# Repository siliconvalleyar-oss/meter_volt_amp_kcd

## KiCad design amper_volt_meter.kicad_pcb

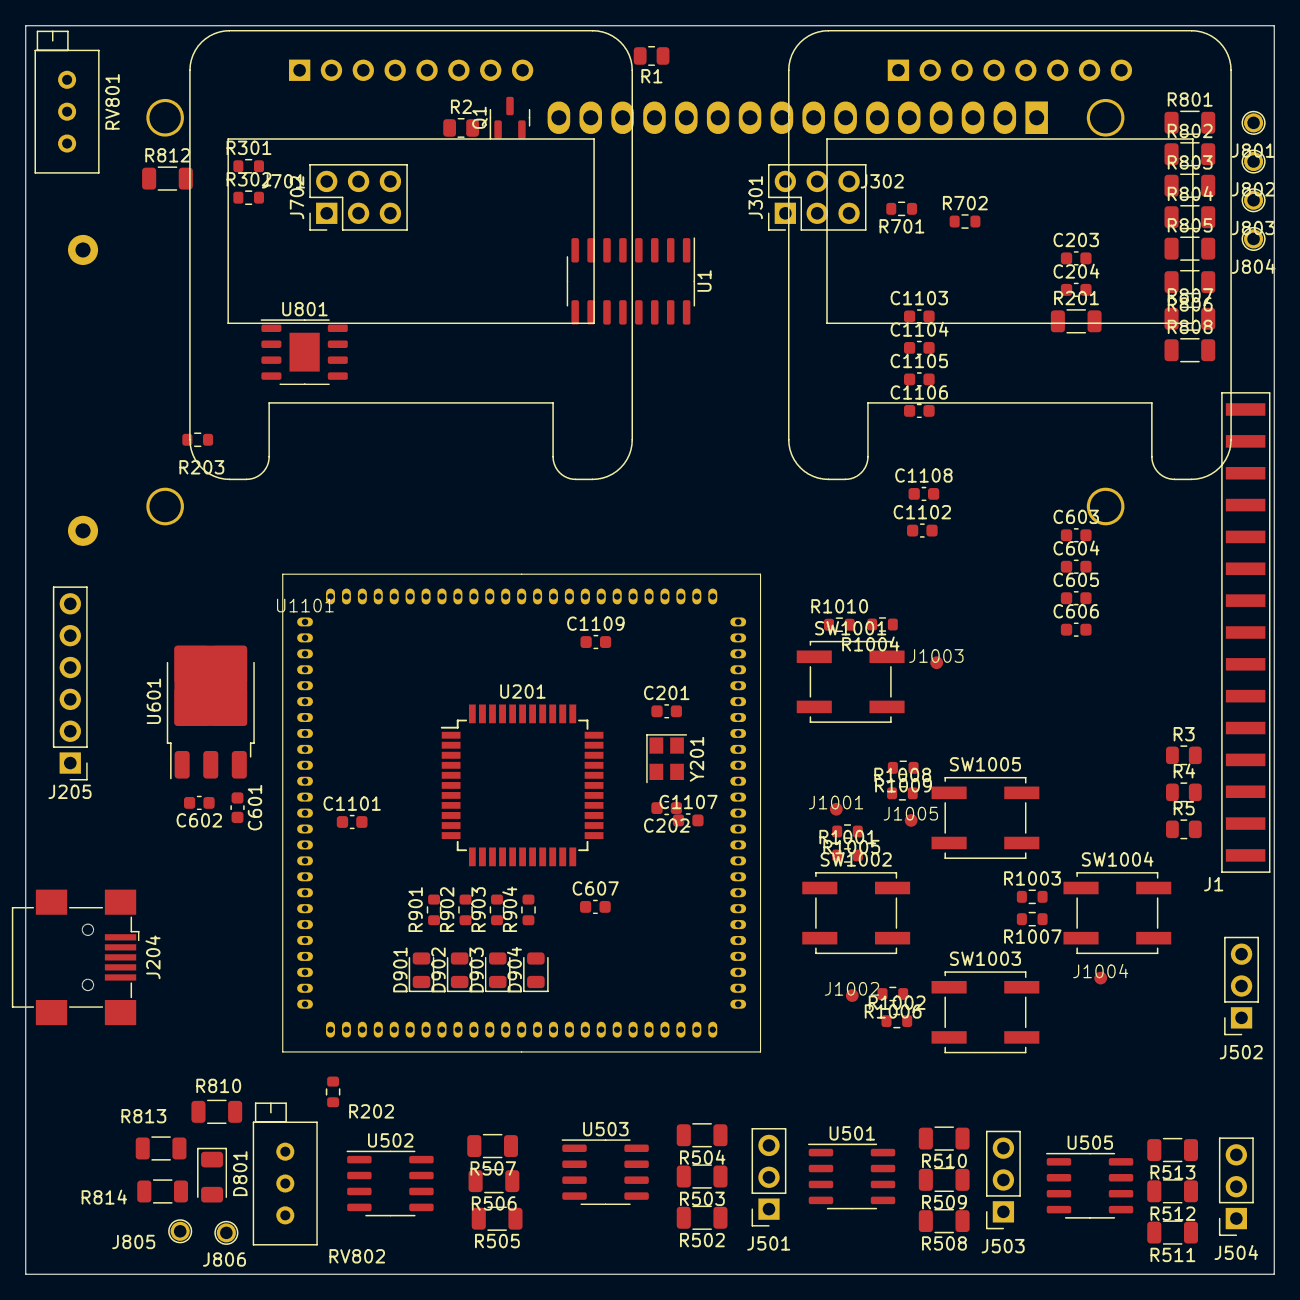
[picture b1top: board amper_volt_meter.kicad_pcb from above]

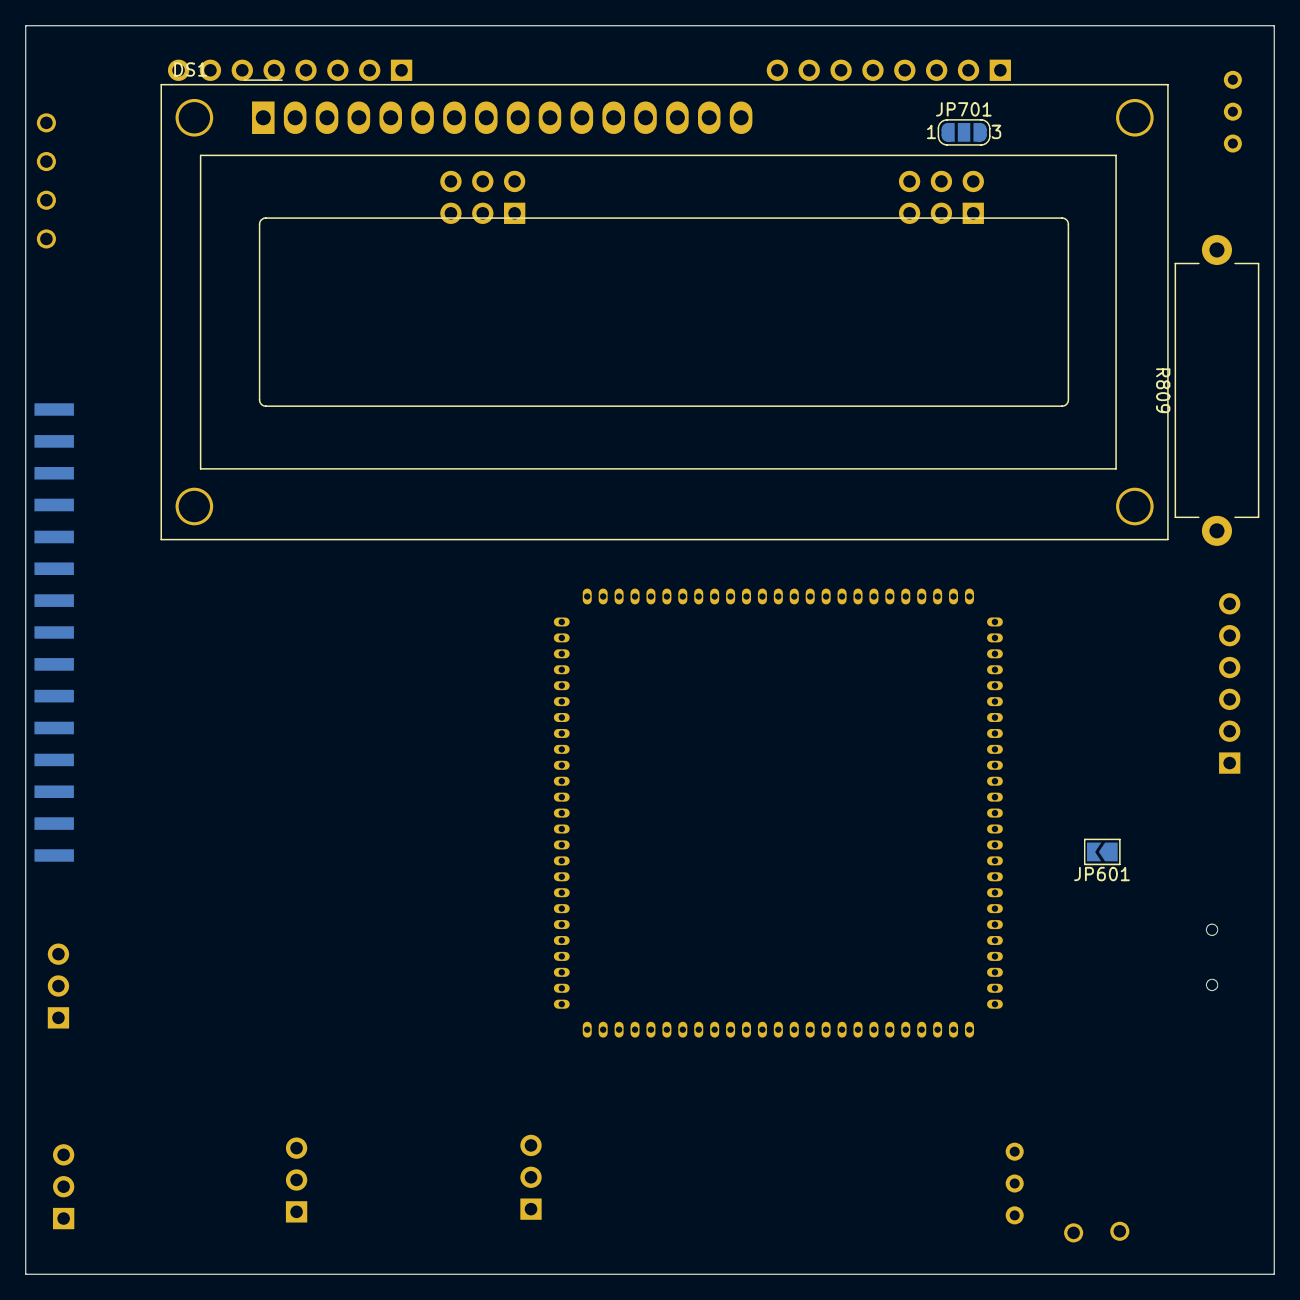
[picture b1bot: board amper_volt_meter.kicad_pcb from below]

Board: 2 copper layers, 99.6 x 99.6 mm, 119 parts (4 on the bottom side), 107 nets, no tracks yet.

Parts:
C201, C202, C203, C204, C601, C602, C603, C604, C605, C606, C607, C1101, C1102, C1103, C1104, C1105, C1106, C1107, C1108, C1109: 100n; C_0805_2012Metric
D801: D_Zener_Small; D_1206_3216Metric
D901: LED_RD0; D_0805_2012Metric
D902: LED_RD1; D_0805_2012Metric
D903: LED_RD2; D_0805_2012Metric
D904: LED_RD3; D_0805_2012Metric
DS1: WC1602A
J1: Conn_02x15_Odd_Even; PinHeader_2x15_P2.54mm_Vertical_edge_mount_smd
J204: USB_B_Mini; USB_Mini-B_Wuerth_65100516121_Horizontal
J205: pickit; PinHeader_1x06_P2.54mm_Vertical
J301, J702: OledSpiST1306; PinHeader_2x03_P2.54mm_Vertical
J302, J701: OledSpiST7789; Adafruit_SSD1306_No_Mounting_Holes_pads
J501, J502, J503, J504: potenciometer_digital_0; PinSocket_1x03_P2.54mm_Vertical
J801, J802, J803, J804, J805, J806: tp?; Pin_D1.5mmx1mm
J1001, J1002, J1003, J1004, J1005: buttons; pin_1016_mm
JP601: SolderJumper_2_Open; SolderJumper-2_P1.3mm_Open_TrianglePad1.0x1.5mm
JP701: select 3v3 or 5v; SolderJumper-3_P1.3mm_Open_RoundedPad1.0x1.5mm_NumberLabels
Q1: Q_NPN_BCE; SOT-23
R1, R2, R3, R4, R5, R301, R302, R701, R702: 10K; R_0805_2012Metric
R201: 0; R_1206_3216Metric
R202, R203: 27; R_0805_2012Metric
R502, R503, R504, R505, R506, R507, R508, R509, R510, R511, R512, R513: 4K7; R_1206_3216Metric
R801, R803, R805, R807: 10k; R_1206_3216Metric
R802, R804, R806, R808: 1k; R_1206_3216Metric
R809: 0R33; R_Axial_Power_L20.0mm_W6.4mm_P22.40mm
R810: R; R_1206_3216Metric
R812, R813, R814: 2K7; R_1206_3216Metric
R901, R902, R903, R904: 2k2; R_0805_2012Metric
R1001, R1002, R1003, R1004, R1005, R1006, R1007, R1008, R1009, R1010: 4K7; R_0805_2012Metric
RV801, RV802: 1K; Potentiometer_Bourns_3296X_Horizontal
SW1001, SW1002, SW1003, SW1004, SW1005: switch; SW_Push_1P1T_NO_CK_KSC6xxJ
U1: 74HC595; SOIC-16_3.9x9.9mm_P1.27mm
U201: PIC18F46J50-I_PT; TQFP-44_10x10mm_P0.8mm
U501, U502, U503, U505: MCP41010; SOIC-8_3.9x4.9mm_P1.27mm
U601: LM1117DT-3.3; TO-252-3_TabPin2
U801: LM358; HSOP-8-1EP_3.9x4.9mm_P1.27mm_EP2.41x3.1mm
U1101: .; PIM100
Y201: Crystal_GND24_Small; Oscillator_SMD_Abracon_ASE-4Pin_3.2x2.5mm

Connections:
+3.3V: C602.1, C603.1, C604.1, C605.1, C606.1, C607.1, C1101.1, C1102.1, C1103.1, C1104.1, C1105.1, C1106.1, C1107.1, C1108.1, C1109.1, J205.2, J301.1, J302.2, J702.1, JP601.2 (B), JP701.3 (B), R301.1, R302.1, R701.1, R702.1, R801.1, R803.1, R805.1, R807.1, R1005.1, R1006.1, R1007.1, R1009.1, R1010.1, U201.7 (VDD), U201.28 (VDD), U501.8 (VDD), U502.8 (VDD), U503.8 (VDD), U505.8 (VDD), U601.2 (VO), U801.8 (V+), U1101.2 (VDD), U1101.16 (VDD), U1101.30 (AVDD), U1101.37 (VDD), U1101.46 (VDD), U1101.55 (VUSB3V3), U1101.62 (VDD), U1101.85 (VCAP/VDDCORE), U1101.86 (VDD)
+5F: C601.1, DS1.2 (VDD), J301.2, J301.4, J702.2, J702.4, JP601.1 (A), JP701.1 (A), R1.1, R3.1, R201.1, U1.12 (RCLK), U1.16 (VCC), U601.3 (VI)
/Analogs_Control/ra_2: J803.1, R805.2, R806.1
/Analogs_Control/ra_3: J804.1, R807.2, R808.1
/oS_AnalogDevices/GND: J1.19, J1.20, J1.25, J1.26
/ucontroller_pic18F46j50/VUSB: C203.1, C204.1, U201.37 (VUSB)
/ucontroller_pic18F46j50/d+: R202.1, U201.43 (RC5/D+/VP)
/ucontroller_pic18F46j50/d-: R203.1, U201.42 (RC4/D-/VM)
AMPER: R809.1, U801.5 (+)
AN8: R812.2, U201.10 (RB2/AN8/CTEDG1/PMA3/VMO/REFO/RP5), U801.1, U1101.22 (RB3)
AN9: J801.1, R801.2, R802.1, U201.11 (RB3/AN9/CTEDG2/PMA2/VPO/RP6), U1101.21 (RB4)
AN10: J802.1, R803.2, R804.1, U201.9 (RB1/AN10/PMBE/RTCC/RP4), U1101.20 (RB5)
BLK_RPI: J302.7, J701.7
DC_RPI: J302.6, J701.6
GND: C201.2, C202.2, C203.2, C204.2, C601.2, C602.2, C603.2, C604.2, C605.2, C606.2, C607.2, C1101.2, C1102.2, C1103.2, C1104.2, C1105.2, C1106.2, C1107.2, C1108.2, C1109.2, D801.2 (A), D901.1 (K), D902.1 (K), D903.1 (K), D904.1 (K), DS1.1 (VSS), DS1.5 (R/W), J204.5 (GND), J204.6 (Shield), J205.3, J301.6, J302.1, J701.1, J702.6, Q1.3 (E), R4.2, R802.2, R804.2, R806.2, R808.2, R809.2, R810.2, R814.1, RV801.3, SW1001.1 (C), SW1002.1 (C), SW1003.1 (C), SW1004.1 (C), SW1005.1 (C), U1.8 (GND), U1.13 (~OE), U201.6 (VSS), U201.29 (VSS), U501.4 (VSS), U502.4 (VSS), U503.4 (VSS), U505.4 (VSS), U601.1 (GND), U801.4 (V-), Y201.2, Y201.4
GPIO20: J1001.1, R1001.1, R1005.2
GPIO21: J1002.1, R1002.1, R1006.2
GPIO22: J1003.1, R1004.1, R1010.2
GPIO23: J1004.1, R1003.1, R1007.2
GPIO24: J1005.1, R1008.1, R1009.2
unnamed: D801.1 (K), R813.1, R814.2
unnamed: D901.2 (A), R901.1
unnamed: D902.2 (A), R902.1
unnamed: D903.2 (A), R903.1
unnamed: D904.2 (A), R904.1
unnamed: DS1.7 (D0), U1.15 (QA)
unnamed: DS1.8 (D1), U1.1 (QB)
unnamed: DS1.9 (D2), U1.2 (QC)
unnamed: DS1.10 (D3), U1.3 (QD)
unnamed: DS1.11 (D4), U1.4 (QE)
unnamed: DS1.12 (D5), U1.5 (QF)
unnamed: DS1.13 (D6), U1.6 (QG)
unnamed: DS1.14 (D7), U1.7 (QH)
unnamed: DS1.15 (LED(+)), R1.2
unnamed: DS1.16 (LED(-)), Q1.2 (C)
unnamed: J204.3 (D+), R203.2
unnamed: J204.2 (D-), R202.2
unnamed: J204.1 (VBUS), R201.2
unnamed: J501.1, R502.1
unnamed: J501.2, R503.1
unnamed: J501.3, R504.1
unnamed: J502.1, R505.1
unnamed: J502.2, R506.1
unnamed: J502.3, R507.1
unnamed: J503.1, R508.1
unnamed: J503.2, R509.1
unnamed: J503.3, R510.1
unnamed: J504.1, R511.1
unnamed: J504.2, R512.1
unnamed: J504.3, R513.1
unnamed: J701.2, JP701.2 (C)
unnamed: J805.1, RV802.1
unnamed: J806.1, RV802.2
unnamed: Q1.1 (B), R2.2
unnamed: R812.1, RV801.2
unnamed: R813.2, RV802.3
unnamed: R1004.2, SW1001.2 (D)
unnamed: R1001.2, SW1002.2 (D)
unnamed: R1002.2, SW1003.2 (D)
unnamed: R1003.2, SW1004.2 (D)
unnamed: R1008.2, SW1005.2 (D)
unnamed: U201.12 (NC), U201.13 (NC), U201.33 (NC), U201.34 (NC)
unnamed: C202.1, U201.30 (OSC1/CLKI/RA7), Y201.3
unnamed: C201.1, U201.31 (OSC2/CLKO/RA6), Y201.1
unnamed: R508.2, U501.5 (PA0)
unnamed: R510.2, U501.7 (PB0)
unnamed: R509.2, U501.6 (PW0)
unnamed: R505.2, U502.5 (PA0)
unnamed: R507.2, U502.7 (PB0)
unnamed: R506.2, U502.6 (PW0)
unnamed: R502.2, U503.5 (PA0)
unnamed: R504.2, U503.7 (PB0)
unnamed: R503.2, U503.6 (PW0)
unnamed: R511.2, U505.5 (PA0)
unnamed: R513.2, U505.7 (PB0)
unnamed: R512.2, U505.6 (PW0)
unnamed: U801.3 (+), U801.6 (-), U801.7
unnamed: R810.1, U801.2 (-)
unnamed: U1101.15 (VSS), U1101.36 (VSS), U1101.45 (VSS), U1101.65 (VSS), U1101.75 (VSS)
RA0: U201.19 (RA0/AN0/C1INA/ULPWU/PMA6/RP0), U1101.17 (RA0/TMS)
RA1: U201.20 (RA1/AN1/C2INA/PMA7/RP1), U1101.38 (RA1/TCK)
RA5: U201.24 (RA5/AN4/~SS1/HLVDIN/RCV/RP2), U1101.61 (RA5/TDO)
RB0: U201.8 (RB0/AN12/INT0/RP3), U1101.23 (RB2)
RC0: R2.1, U201.32 (RC0/T1OSO/T1CKI/RP11)
RC1: U1.14 (SER), U201.35 (RC1/T1OSI/~UOE/RP12), U1101.6 (RC1)
RC6: U201.44 (RC6/PMA5/TX1/CK1/RP17), U501.2 (SCK), U501.3 (SI), U502.2 (SCK), U503.2 (SCK), U505.2 (SCK), U505.3 (SI)
RC7: U201.1 (RC7/PMA4/RX1/DT1/SDO1/RP18), U502.3 (SI), U503.3 (SI)
RD2: DS1.6 (E), U201.40 (RD2/PMD2/RP19), U1101.77 (RD2)
RD3: DS1.4 (RS), U201.41 (RD3/PMD3/RP20), U1101.78 (RD3)
RD4: R901.2, U201.2 (RD4/PMD4/RP21), U1101.81 (RD4)
RD5: R902.2, U201.3 (RD5/PMD5/RP22), U1101.82 (RD5)
RD6: R903.2, U201.4 (RD6/PMD6/RP23), U1101.83 (RD6)
RD7: R904.2, U201.5 (RD7/PMD7/RP24), U1101.84 (RD7)
RE0: U201.25 (RE0/AN5/PMRD), U503.1 (~CS), U1101.93 (RE0)
RE1: U1.10 (~SRCLR), U201.26 (RE1/AN6/PMWR), U502.1 (~CS), U1101.94 (RE1)
RE2: U1.11 (SRCLK), U201.27 (RE2/AN7/PMCS), U501.1 (~CS), U1101.98 (RE2)
RES_RPI: J302.5, J701.5
SCL_1: J302.3, J701.3, U201.14 (RB4/PMA1/KBI0/SCK1/SCL1/RP7)
SCL_2: J301.5, J702.5, R301.2, R701.2, U201.38 (RD0/PMD0/SCL2)
SDA_1: J302.4, J701.4, U201.15 (RB5/PMA0/KBI1/SDI1/SDA1/RP8)
SDA_2: J301.3, J702.3, R302.2, R702.2, U201.39 (RD1/PMD1/SDA2)
VO: DS1.3 (VO), R5.2
VREF+: U201.22 (RA3/AN3/VREF+/C1INB), U1101.59 (RA3)
VREF-: U201.21 (RA2/AN2/VREF-/CVREF-/C2INB), U1101.58 (RA2)
mclr: J205.1, U201.18 (~MCLR), U1101.13 (~MCLR)
pgc: J205.5, U201.16 (RB6/KBI2/PGC/RP9)
pgd: J205.4, U201.17 (RB7/KBI3/PGD/RP10)
